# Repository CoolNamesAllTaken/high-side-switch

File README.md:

# high-side-switch
High side load switch for automotive and aerospace applications.

[Design Notes](word/design_notes_high_side_switch.pdf)

[Design Presentation](affinity/Onsite_Presentation_Reliable_Robotics.pdf)

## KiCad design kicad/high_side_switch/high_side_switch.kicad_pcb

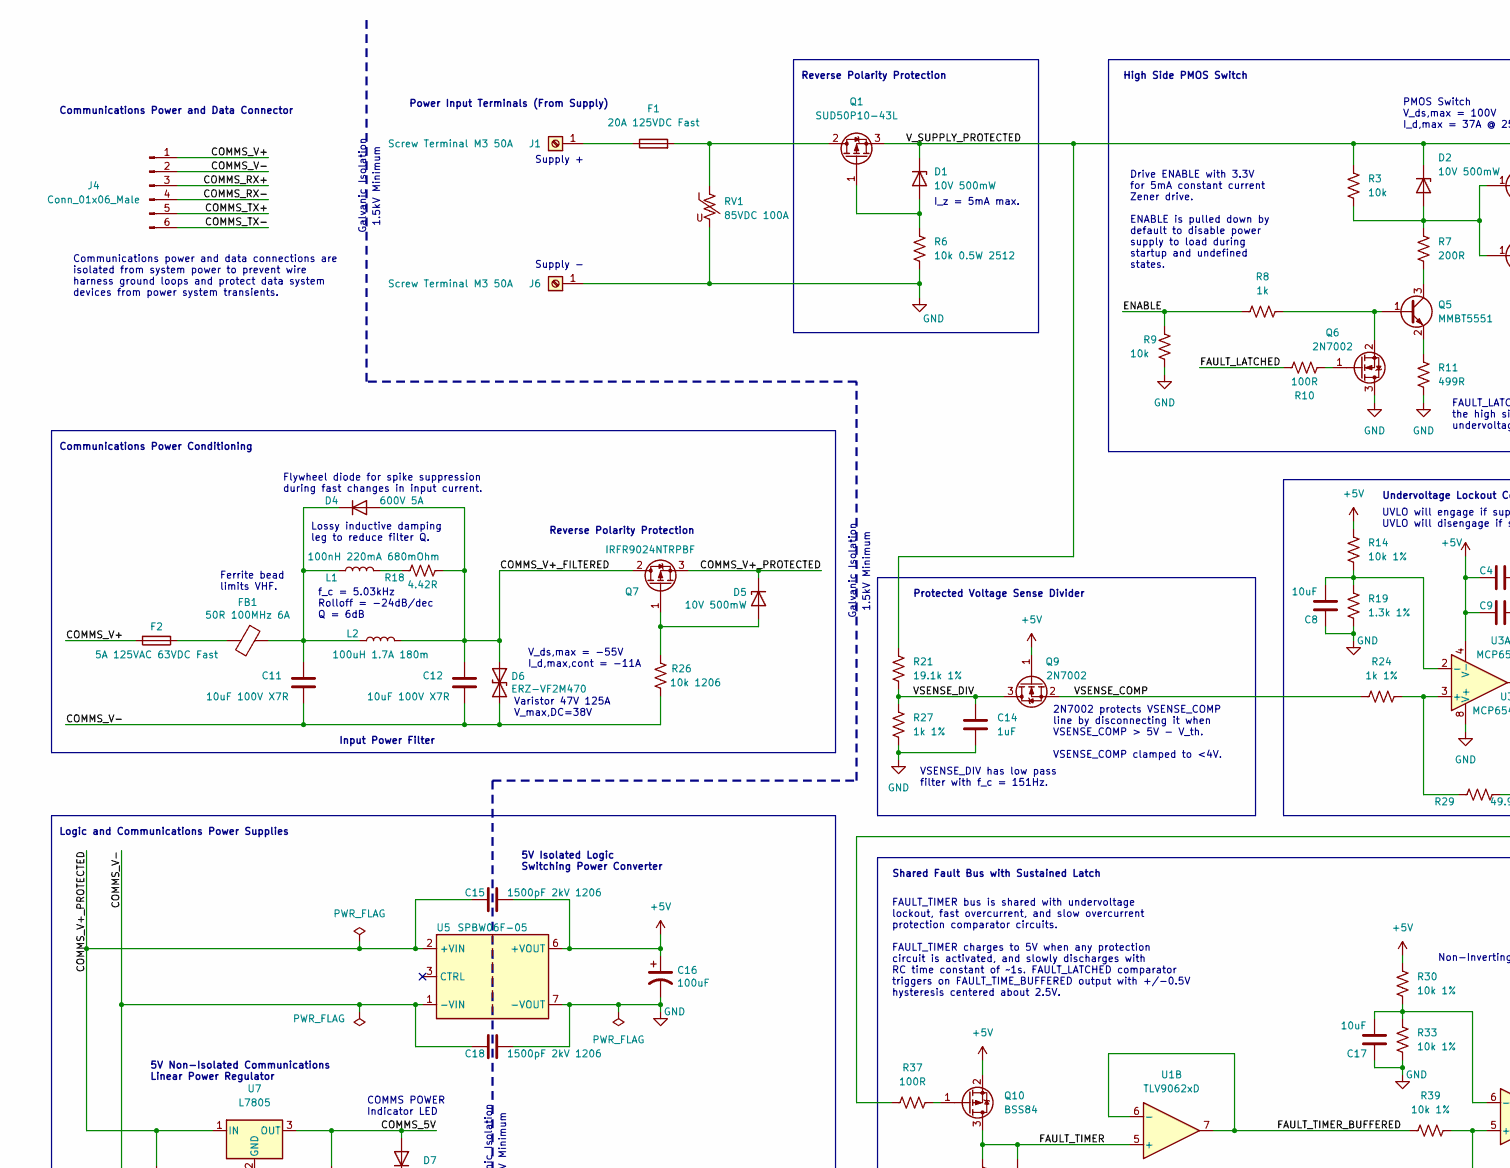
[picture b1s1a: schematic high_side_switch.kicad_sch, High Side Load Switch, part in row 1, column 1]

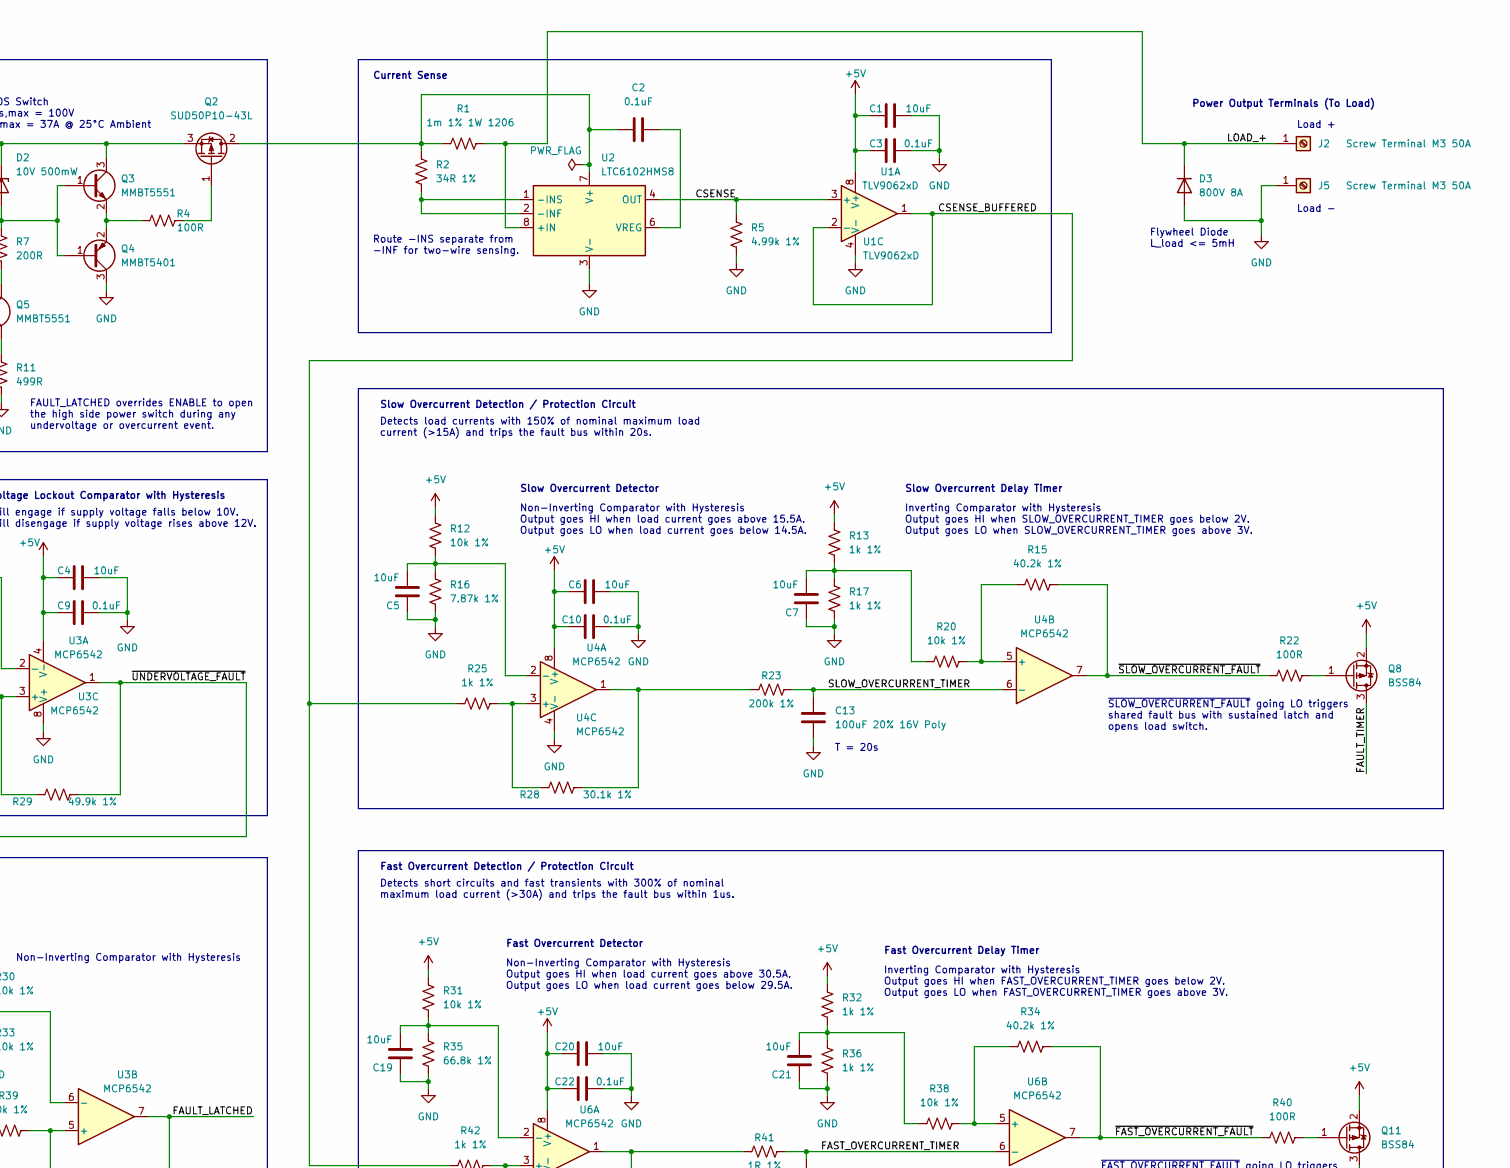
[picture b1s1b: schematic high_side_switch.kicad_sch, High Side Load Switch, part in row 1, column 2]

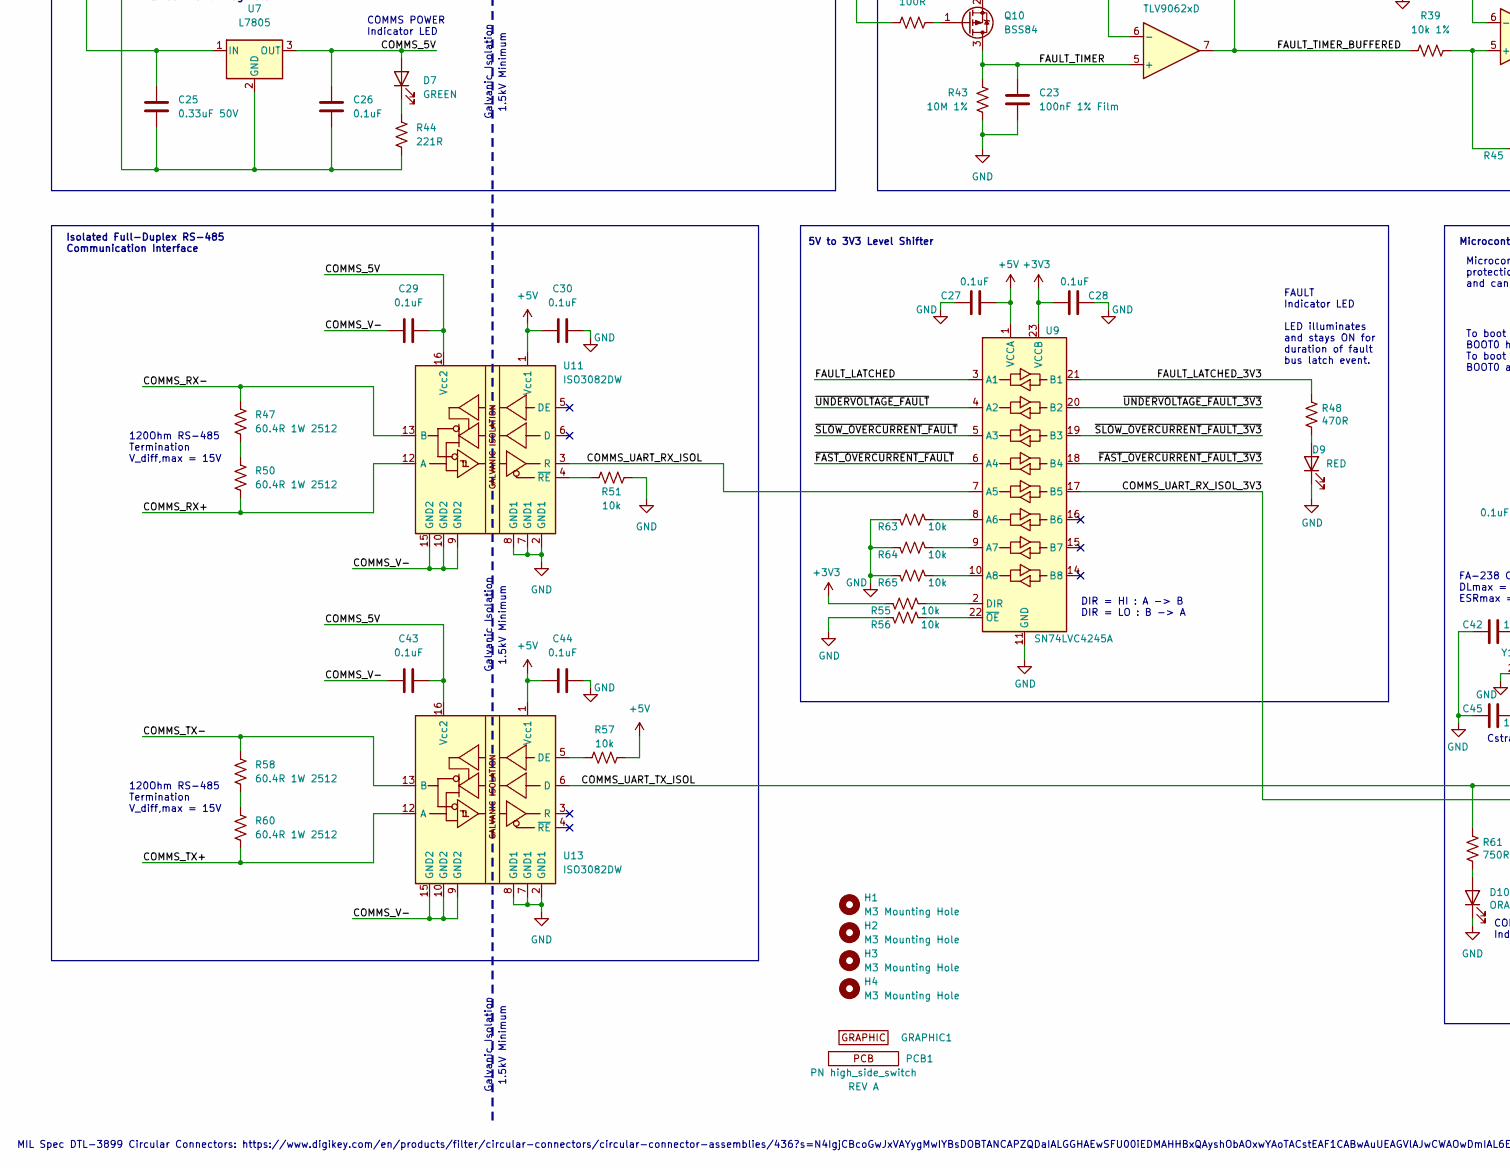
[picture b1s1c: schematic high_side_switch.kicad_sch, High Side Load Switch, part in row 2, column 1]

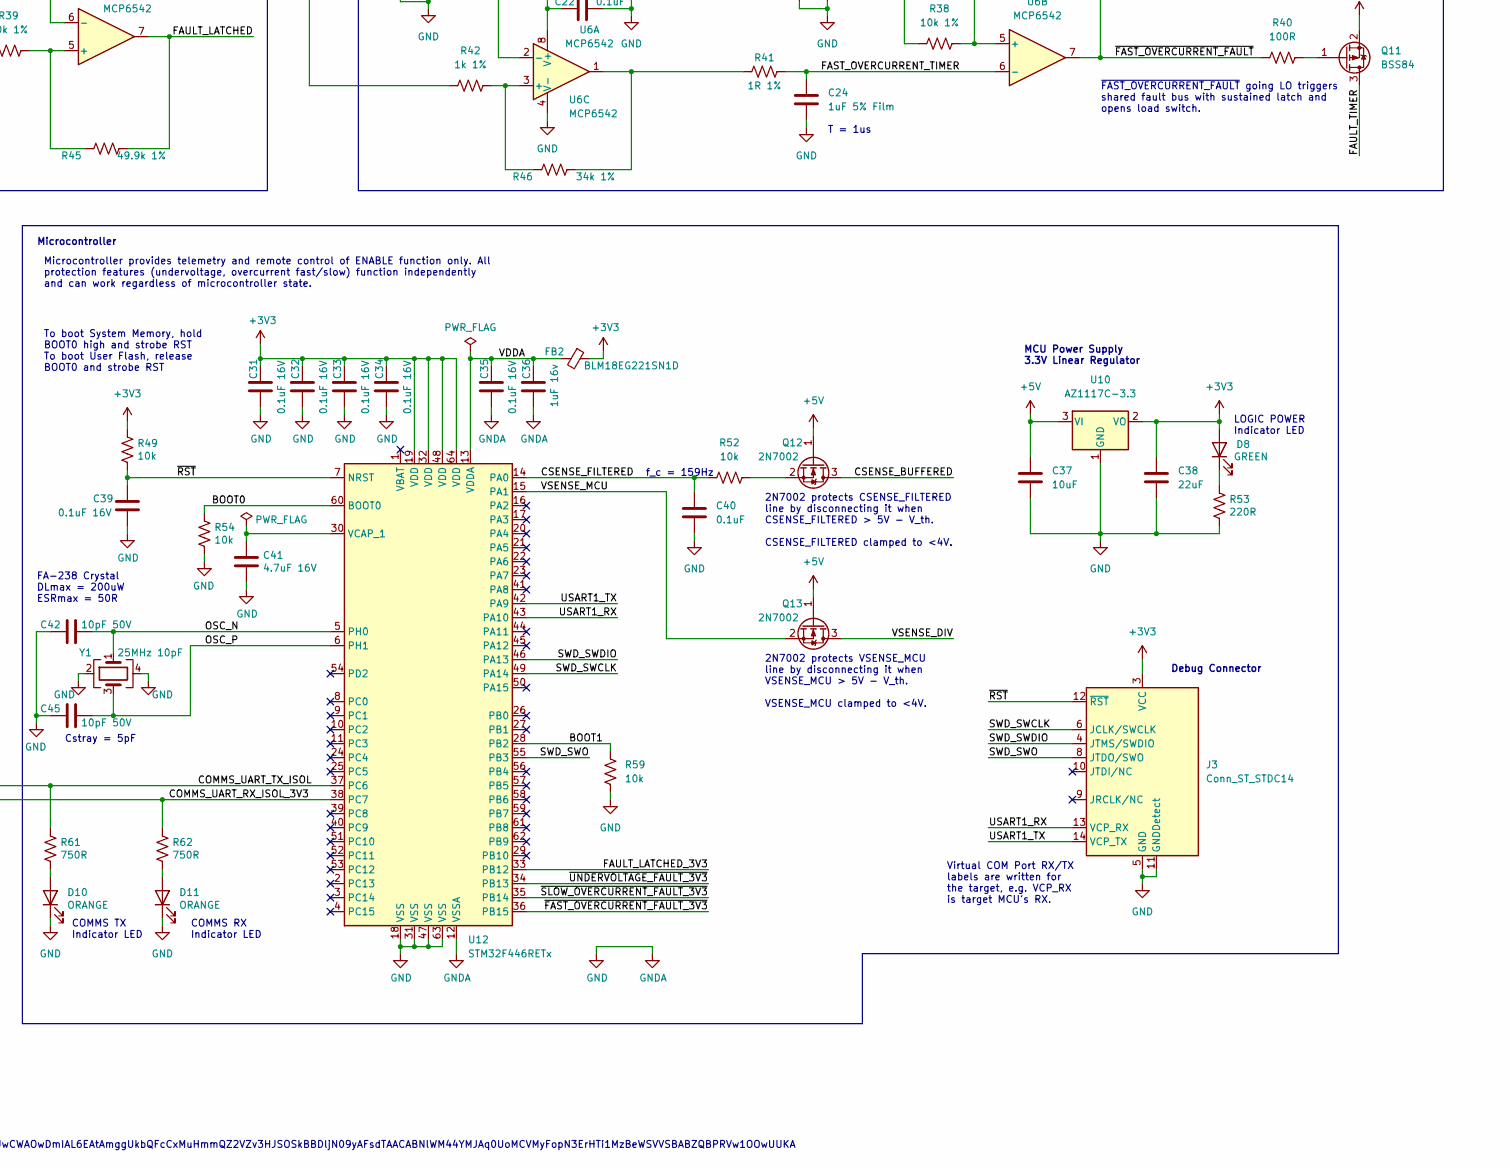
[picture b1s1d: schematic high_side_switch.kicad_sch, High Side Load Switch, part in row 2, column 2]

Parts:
C1, C4, C5, C6, C7, C8, C17, C19, C20, C21, C37: 10uF; C_0603_1608Metric
C2, C3, C9, C10, C22, C26, C29, C30, C40, C43, C44: 0.1uF; C_0603_1608Metric
C11, C12: 10uF 100V X7R; C_2220_5650Metric; MPN 22201C106MAT2A
C13: 100uF 20% 16V Poly; CP_Elec_6.3x5.9; MPN 16SVPC100M
C14: 1uF; C_0603_1608Metric
C15, C18: 1500pF 2kV 1206; C_1206_3216Metric; MPN C1206C152KGRACAUTO
C16: 100uF; CP_Elec_6.3x5.9; MPN 16SVPC100M
C23: 100nF 1% Film; C_Rect_L7.2mm_W2.5mm_P5.00mm_FKS2_FKP2_MKS2_MKP2; MPN R82DC3100DQ50J
C24: 1uF 5% Film; C_Rect_L7.2mm_W5.5mm_P5.00mm_FKS2_FKP2_MKS2_MKP2; MPN R82EC4100DQ70J
C25: 0.33uF 50V; C_0805_2012Metric
C27, C28: 0.1uF; C_0603_1608Metric; MPN CL10B104MB8NNNC
C31, C32, C33, C34, C35, C39: 0.1uF 16V; C_0402_1005Metric; MPN CL05B104KO5NNNC
C36: 1uF 16v; C_0402_1005Metric; MPN CL05A105KO5NNNC
C38: 22uF; C_0805_2012Metric
C41: 4.7uF 16V; C_0402_1005Metric; MPN CL05A475MO5NUNC
C42, C45: 10pF 50V; C_0402_1005Metric; MPN CC0402JRNPO9BN100
D1, D2, D5: 10V 500mW; D_SOD-123; MPN BZT52C10-7-F
D3: 800V 8A; D_SMC; MPN S8KC-13
D4: 600V 5A; D_SMB; MPN SD560BTR
D6: ERZ-VF2M470; Panasonic_ZNR-VF; MPN ERZ-VF2M470
D7, D8: GREEN; LED_0603_1608Metric; MPN SML-D13M8WT86
D9: RED; LED_0603_1608Metric; MPN SML-D12U8WT86
D10, D11: ORANGE; LED_0603_1608Metric; MPN SML-D12D8WT86
F1: 20A 125VDC Fast; Fuse_BelFuse_0679L; MPN 0679L9200-05
F2: 5A 125VAC 63VDC Fast; R_1206_3216Metric; MPN C1Q 5
FB1: 50R 100MHz 6A; L_1206_3216Metric; MPN 2512065007Y6
FB2: BLM18EG221SN1D; L_0603_1608Metric; MPN BLM18EG221SN1D
GRAPHIC1: Graphic; bird_with_pants_small_flipped
H1, H2, H3, H4: M3 Mounting Hole; MountingHole_3.2mm_M3
J1, J2, J5, J6: Screw Terminal M3 50A; Wuerth_Redcube_74650073R_M3; MPN 74650073R
J3: Conn_ST_STDC14; PinHeader_2x07_P1.27mm_Vertical_SMD; MPN FTSH-107-01-L-DV-K
J4: Conn_01x06_Male; Molex_Micro-Fit_3.0_43045-0612_2x03_P3.00mm_Vertical; MPN 0430450612
L1: 100nH 220mA 680mOhm; L_0603_1608Metric; MPN LQW18ANR10J00D
L2: 100uH 1.7A 180m; L_Bourns_SRR1260; MPN SRR1260-101M
PCB1: PCB; PCB_PN_REV; MPN PN high_side_switch
Q1, Q2: SUD50P10-43L; TO-252-3_TabPin2; MPN SUD50P10-43L-GE3
Q3, Q5: MMBT5551; SOT-23; MPN MMBT5551-7-F
Q4: MMBT5401; SOT-23; MPN MMBT5401-7-F
Q6, Q9, Q12, Q13: 2N7002; SOT-23
Q7: IRFR9024NTRPBF; TO-252-2; MPN IRFR9024NTRPBF
Q8, Q10, Q11: BSS84; SOT-23
R1: 1m 1% 1W 1206; R_1206_3216Metric; MPN CSNL1206FT1L00
R2: 34R 1%; R_0603_1608Metric
R3, R9, R49, R51, R52, R54, R57, R59: 10k; R_0603_1608Metric
R4, R10, R22, R37, R40: 100R; R_0603_1608Metric
R5: 4.99k 1%; R_0603_1608Metric
R6: 10k 0.5W 2512; R_2512_6332Metric
R7: 200R; R_0603_1608Metric
R8: 1k; R_0603_1608Metric
R11: 499R; R_0603_1608Metric
R12, R14, R20, R30, R31, R33, R38, R39: 10k 1%; R_0603_1608Metric
R13, R17, R24, R25, R27, R32, R36, R42: 1k 1%; R_0603_1608Metric
R15, R34: 40.2k 1%; R_0603_1608Metric
R16: 7.87k 1%; R_0603_1608Metric
R18: 4.42R; R_0603_1608Metric; MPN RC0603FR-074R42L
R19: 1.3k 1%; R_0603_1608Metric
R21: 19.1k 1%; R_0603_1608Metric
R23: 200k 1%; R_0603_1608Metric
R26: 10k 1206; R_1206_3216Metric; MPN RC1206FR-0710KL
R28: 30.1k 1%; R_0603_1608Metric
R29, R45: 49.9k 1%; R_0603_1608Metric
R35: 66.8k 1%; R_0603_1608Metric
R41: 1R 1%; R_0603_1608Metric
R43: 10M 1%; R_0603_1608Metric
R44: 221R; R_0603_1608Metric
R46: 34k 1%; R_0603_1608Metric
R47, R50, R58, R60: 60.4R 1W 2512; R_2512_6332Metric; MPN RMCF2512FT60R4
R48: 470R; R_0603_1608Metric
R53: 220R; R_0603_1608Metric
R55, R56, R63, R64, R65: 10k; R_0603_1608Metric; MPN RC0603FR-0710KL
R61, R62: 750R; R_0603_1608Metric
RV1: 85VDC 100A; Fuse_1206_3216Metric; MPN B72520T0600K062
U1: TLV9062xD; SOIC-8_3.9x4.9mm_P1.27mm
U2: LTC6102HMS8; MSOP-8_3x3mm_P0.65mm; MPN LTC6102HMS8#TRPBF
U3, U4, U6: MCP6542; SOIC-8_3.9x4.9mm_P1.27mm; MPN MCP6542T-I/SN
U5: SPBW06F-05; Converter_DCDC_TRACO_TMR-xxxx_THT; MPN SPBW06F-05
U7: L7805; TO-252-3_TabPin2; MPN L7805ABD2T-TR
U9: SN74LVC4245A; TSSOP-24_4.4x7.8mm_P0.65mm; MPN SN74LVC4245APWR
U10: AZ1117C-3.3; SOT-89-3; MPN AZ1117CR-3.3TRG1
U11, U13: ISO3082DW; SOIC-16W_7.5x10.3mm_P1.27mm; MPN ISO3082DWR
U12: STM32F446RETx; LQFP-64_10x10mm_P0.5mm; MPN STM32F446RET6
Y1: 25MHz 10pF; Crystal_SMD_SeikoEpson_FA238-4Pin_3.2x2.5mm; MPN FA-238 25.0000MB-K3

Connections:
+3V3: C28.2, C31.1, C32.1, C33.1, C34.1, C38.1, D8.2 (A), FB2.1, J3.3 (VCC), R49.1, R55.1, U9.23 (VCCB), U9.24 (VCCB), U10.2 (VO), U12.19 (VDD), U12.32 (VDD), U12.48 (VDD), U12.64 (VDD)
+5V: C1.1, C3.1, C4.1, C6.1, C9.1, C10.1, C15.2, C16.1, C20.1, C22.1, C27.2, C30.1, C37.1, C44.1, Q8.2 (S), Q9.1 (G), Q10.2 (S), Q11.2 (S), Q12.1 (G), Q13.1 (G), R12.1, R13.1, R14.1, R30.1, R31.1, R32.1, R57.2, U1.8 (V+), U3.4 (V-), U4.8 (V+), U5.6 (+VOUT), U6.8 (V+), U9.1 (VCCA), U10.3 (VI), U11.1 (Vcc1), U13.1 (Vcc1)
/BOOT0: R54.1, U12.60 (BOOT0)
/BOOT1: R59.1, U12.28 (PB2)
/COMMS_5V: C26.1, C29.2, C43.2, D7.2 (A), U7.3 (OUT), U11.16 (Vcc2), U13.16 (Vcc2)
/COMMS_RX+: J4.3, R50.2, U11.12 (A)
/COMMS_RX-: J4.4, R47.1, U11.13 (B)
/COMMS_TX+: J4.5, R60.2, U13.12 (A)
/COMMS_TX-: J4.6, R58.1, U13.13 (B)
/COMMS_UART_RX_ISOL: U9.7 (A5), U11.3 (R)
/COMMS_UART_RX_ISOL_3V3: R62.1, U9.17 (B5), U12.38 (PC7)
/COMMS_UART_TX_ISOL: R61.1, U12.37 (PC6), U13.6 (D)
/COMMS_V+: F2.2, J4.1
/COMMS_V+_FILTERED: C12.1, D4.2 (A), D6.1 (A1), L2.2, Q7.2 (D), R18.1
/COMMS_V+_PROTECTED: C15.1, C25.1, D5.1 (K), Q7.3 (S), U5.2 (+VIN), U7.1 (IN)
/COMMS_V-: C11.2, C12.2, C18.1, C25.2, C26.2, C29.1, C43.1, D6.2 (A2), J4.2, R26.1, R44.2, U5.1 (-VIN), U7.2 (GND), U11.9 (GND2), U11.10 (GND2), U11.15 (GND2), U13.9 (GND2), U13.10 (GND2), U13.15 (GND2)
/CSENSE: R5.1, U1.3 (+), U2.4 (OUT)
/CSENSE_BUFFERED: Q12.3 (D), R25.1, R42.1, U1.1, U1.2 (-)
/CSENSE_FILTERED: C40.1, R52.1, U12.14 (PA0)
/ENABLE: R8.1, R9.1
/FAST_OVERCURRENT_TIMER: C24.1, R41.2, U6.6 (-)
/FAULT_LATCHED: R10.1, R45.2, U3.7, U9.3 (A1)
/FAULT_LATCHED_3V3: R48.1, U9.21 (B1), U12.33 (PB12)
/FAULT_TIMER: C23.1, Q8.3 (D), Q10.3 (D), Q11.3 (D), R43.1, U1.5 (+)
/FAULT_TIMER_BUFFERED: R39.1, U1.6 (-), U1.7
/LOAD_+: D3.1 (K), J2.1, R1.2, U2.8 (+IN)
/OSC_N: C42.2, U12.5 (PH0), Y1.1
/OSC_P: C45.2, U12.6 (PH1), Y1.3
/SLOW_OVERCURRENT_TIMER: C13.1, R23.2, U4.6 (-)
/SWD_SWCLK: J3.6 (JCLK/SWCLK), U12.49 (PA14)
/SWD_SWDIO: J3.4 (JTMS/SWDIO), U12.46 (PA13)
/SWD_SWO: J3.8 (JTDO/SWO), U12.55 (PB3)
/USART1_RX: J3.13 (VCP_RX), U12.43 (PA10)
/USART1_TX: J3.14 (VCP_TX), U12.42 (PA9)
/VDDA: C35.1, C36.1, FB2.2, U12.13 (VDDA)
/VSENSE_COMP: Q9.2 (S), R24.1
/VSENSE_DIV: C14.1, Q9.3 (D), Q13.3 (D), R21.2, R27.1
/VSENSE_MCU: Q13.2 (S), U12.15 (PA1)
/V_SUPPLY_PROTECTED: D1.1 (K), D2.1 (K), Q1.3 (S), Q2.3 (S), Q3.3 (C), R3.1, R21.1
/~FAST_OVERCURRENT_FAULT_3V3: U9.18 (B4), U12.36 (PB15)
/~FAST_OVERCURRENT_FAULT: R34.2, R40.1, U6.7, U9.6 (A4)
/~RST: C39.1, J3.12 (~RST), R49.2, U12.7 (NRST)
/~SLOW_OVERCURRENT_FAULT_3V3: U9.19 (B3), U12.35 (PB14)
/~SLOW_OVERCURRENT_FAULT: R15.2, R22.1, U4.7, U9.5 (A3)
/~UNDERVOLTAGE_FAULT_3V3: U9.20 (B2), U12.34 (PB13)
/~UNDERVOLTAGE_FAULT: R29.2, R37.1, U3.1, U9.4 (A2)
GND: C1.2, C3.2, C4.2, C5.1, C6.2, C7.1, C8.1, C9.2, C10.2, C13.2, C14.2, C16.2, C17.1, C18.2, C19.1, C20.2, C21.1, C22.2, C23.2, C24.2, C27.1, C28.1, C30.2, C31.2, C32.2, C33.2, C34.2, C35.2, C36.2, C37.2, C38.2, C39.2, C40.2, C41.2, C42.1, C44.2, C45.1, D3.2 (A), D9.1 (K), D10.1 (K), D11.1 (K), J3.5 (GND), J3.7 (GND), J3.11 (GNDDetect), J5.1, J6.1, Q4.3 (C), Q6.3 (D), R5.2, R6.2, R9.2, R11.2, R16.2, R17.2, R19.2, R27.2, R33.2, R35.2, R36.2, R43.2, R51.2, R53.2, R54.2, R56.1, R59.2, R63.1, R64.1, R65.1, RV1.2, U1.4 (V-), U2.3 (V-), U2.5 (V-), U3.8 (V+), U4.4 (V-), U5.7 (-VOUT), U6.4 (V-), U9.11 (GND), U9.12 (GND), U9.13 (GND), U10.1 (GND), U11.2 (GND1), U11.7 (GND1), U11.8 (GND1), U12.12 (VSSA), U12.18 (VSS), U12.31 (VSS), U12.47 (VSS), U12.63 (VSS), U13.2 (GND1), U13.7 (GND1), U13.8 (GND1), Y1.2, Y1.4
unnamed: C2.1, Q2.2 (D), R1.1, R2.1, U2.7 (V+)
unnamed: C2.2, U2.6 (VREG)
unnamed: C5.2, R12.2, R16.1, U4.2 (-)
unnamed: C7.2, R13.2, R17.1, R20.1
unnamed: C8.2, R14.2, R19.1, U3.2 (-)
unnamed: C11.1, D4.1 (K), FB1.1, L1.1, L2.1
unnamed: C17.2, R30.2, R33.1, U3.6 (-)
unnamed: C19.2, R31.2, R35.1, U6.2 (-)
unnamed: C21.2, R32.2, R36.1, R38.1
unnamed: C41.1, U12.30 (VCAP_1)
unnamed: D1.2 (A), Q1.1 (G), R6.1
unnamed: D2.2 (A), Q3.1 (B), Q4.1 (B), R3.2, R7.1
unnamed: D5.2 (A), Q7.1 (G), R26.2
unnamed: D7.1 (K), R44.1
unnamed: D8.1 (K), R53.1
unnamed: D9.2 (A), R48.2
unnamed: D10.2 (A), R61.2
unnamed: D11.2 (A), R62.2
unnamed: F1.1, J1.1
unnamed: F1.2, Q1.2 (D), RV1.1
unnamed: F2.1, FB1.2
unnamed: L1.2, R18.2
unnamed: Q2.1 (G), R4.2
unnamed: Q3.2 (E), Q4.2 (E), R4.1
unnamed: Q5.1 (B), Q6.2 (S), R8.2
unnamed: Q5.2 (E), R11.1
unnamed: Q5.3 (C), R7.2
unnamed: Q6.1 (G), R10.2
unnamed: Q8.1 (G), R22.2
unnamed: Q10.1 (G), R37.2
unnamed: Q11.1 (G), R40.2
unnamed: Q12.2 (S), R52.2
unnamed: R2.2, U2.1 (-INS), U2.2 (-INF)
unnamed: R15.1, R20.2, U4.5 (+)
unnamed: R23.1, R28.2, U4.1
unnamed: R24.2, R29.1, U3.3 (+)
unnamed: R25.2, R28.1, U4.3 (+)
unnamed: R34.1, R38.2, U6.5 (+)
unnamed: R39.2, R45.1, U3.5 (+)
unnamed: R41.1, R46.2, U6.1
unnamed: R42.2, R46.1, U6.3 (+)
unnamed: R47.2, R50.1
unnamed: R51.1, U11.4 (~RE)
unnamed: R55.2, U9.2 (DIR)
unnamed: R56.2, U9.22 (~OE)
unnamed: R57.1, U13.5 (DE)
unnamed: R58.2, R60.1
unnamed: R63.2, U9.8 (A6)
unnamed: R64.2, U9.9 (A7)
unnamed: R65.2, U9.10 (A8)

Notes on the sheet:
Slow Overcurrent Detector
MIL Spec DTL-3899 Circular Connectors: https://www.digikey.com/en/products/filter/circular-connectors/circular-connector-assemblies/436?s=N4IgjCBcoGwJxVAYygMwIYBsDOBTANCAPZQDaIALGGHAEwSFU00iEDMAHHBxQAyshObAOxwYAoTACstEAF1CABwAuUEAGVlAJwCWAOwDmIAL6EAtAmggUkbQFcCxMuHmmQZ2VZv3HJSOSkBBDljN09yAFsdTAACAB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
Non-Inverting Comparator with Hysteresis Output goes HI when load current goes above 30.5A. Output goes LO when load current goes below 29.5A.
Non-Inverting Comparator with Hysteresis
Fast Overcurrent Delay Timer
f_c = 5.03kHz Rolloff = -24dB/dec Q = 6dB
2N7002 protects VSENSE_MCU line by disconnecting it when VSENSE_MCU > 5V - V_th. VSENSE_MCU clamped to <4V.
Galvanic Isolation
Reverse Polarity Protection
Detects load currents with 150% of nominal maximum load current (>15A) and trips the fault bus within 20s.
Lossy inductive damping leg to reduce filter Q.
FAULT_LATCHED overrides ENABLE to open the high side power switch during any undervoltage or overcurrent event.
Input Power Filter
Shared Fault Bus with Sustained Latch
Undervoltage Lockout Comparator with Hysteresis
Flywheel Diode L_load <= 5mH
Slow Overcurrent Delay Timer
FA-238 Crystal DLmax = 200uW ESRmax = 50R
Cstray = 5pF
FAULT Indicator LED LED illuminates and stays ON for duration of fault bus latch event.
1.5kV Minimum
Communications Power and Data Connector
T = 1us
Supply -
UVLO will engage if supply voltage falls below 10V. UVLO will disengage if supply voltage rises above 12V.
I_z = 5mA max.
Isolated Full-Duplex RS-485 Communication Interface
Debug Connector
COMMS TX Indicator LED
Fast Overcurrent Detector
COMMS POWER Indicator LED
Microcontroller
Protected Voltage Sense Divider
Communications Power Conditioning
PMOS Switch V_ds,max = 100V I_d,max = 37A @ 25°C Ambient
Load +
Flywheel diode for spike suppression during fast changes in input current.
5V to 3V3 Level Shifter
COMMS RX Indicator LED
Non-Inverting Comparator with Hysteresis Output goes HI when load current goes above 15.5A. Output goes LO when load current goes below 14.5A.

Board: 4 copper layers, 166 parts (10 on the bottom side), 97 nets, no tracks yet.

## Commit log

2023-01-16 Initial working sim
2023-01-17 Initial release
2023-02-01 Finalize writeup and clean up a bit
2023-02-01 Rename some files
